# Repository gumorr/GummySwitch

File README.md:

# GummySwitch

1 MB ROM switch for Amigas with 1 MB ROM mods (can also work with 2 MB ROMs)

## Use

Position 1-2 on the jumper selects ROM 2 (U4), while position 2-3 selects ROM 1 (U3)

### BOM 
 
|Component|Location|QTY|
|---------|--------|---|
|1x21 Machined Pin Headers|U2|2|
|[42 Pin DIP Socket](https://www.mouser.com/ProductDetail/517-4842-6000-CP)|U3,U4|2|
|[74HCT00 SOIC](https://www.mouser.com/ProductDetail/595-SN74HCT00DE4)|U1|1|
|[0.1uF Ceramic capacitor, 0805](https://www.mouser.com/ProductDetail/581-08055C104K)|C1|1|
|[10K Resistor, 0805](https://www.mouser.com/ProductDetail/754-RR1220P-103D)|R1|1|

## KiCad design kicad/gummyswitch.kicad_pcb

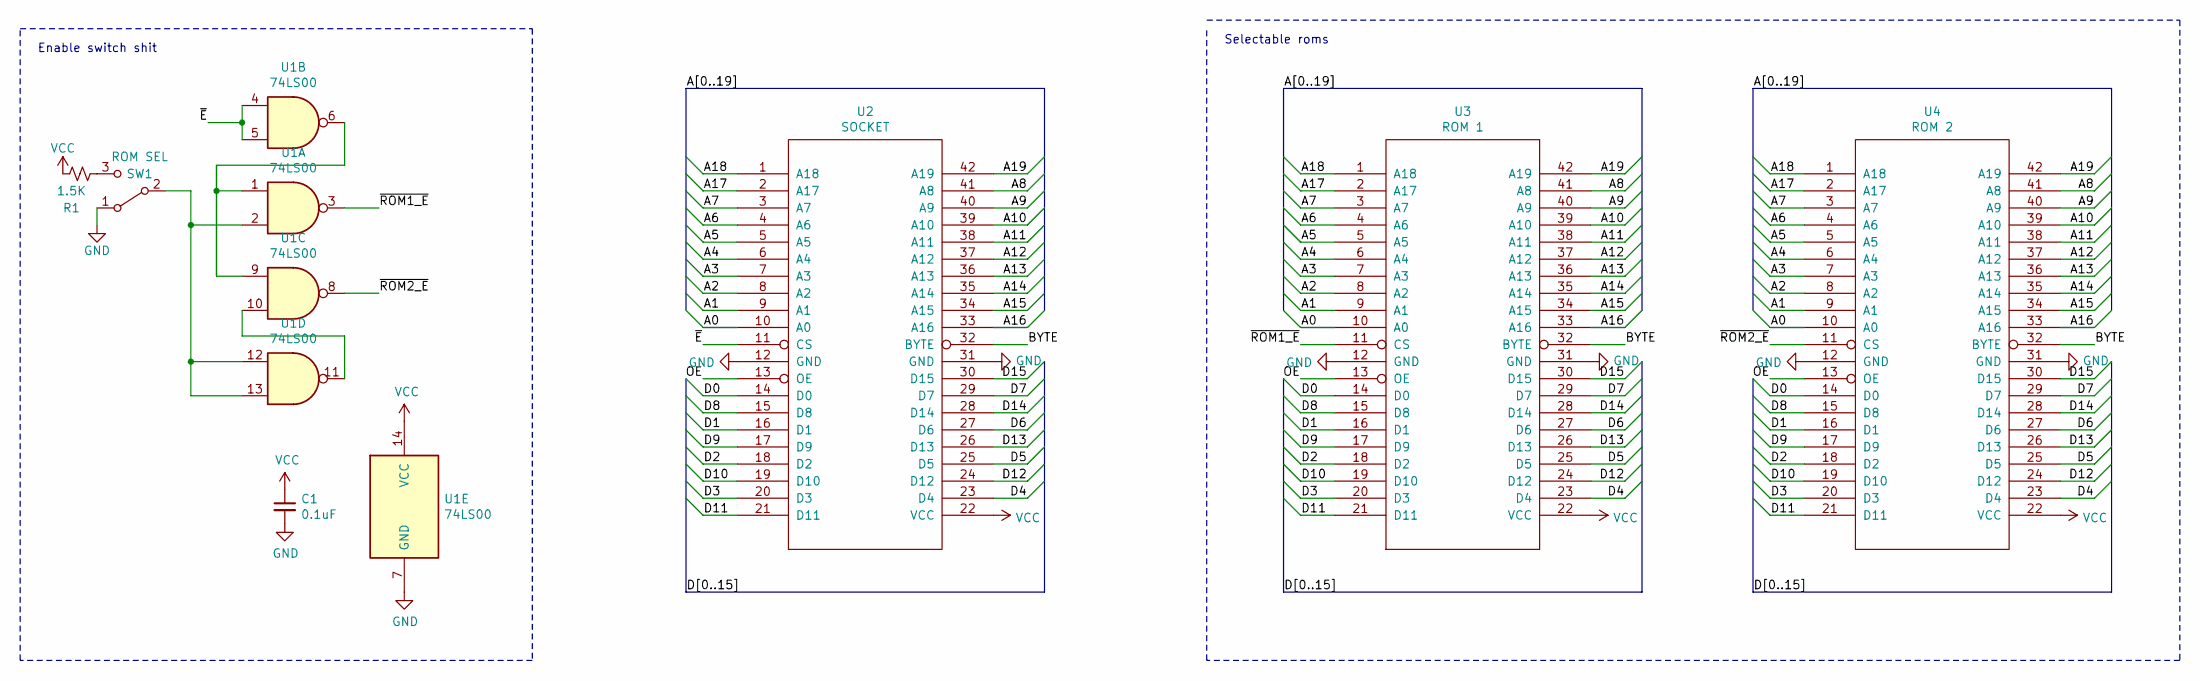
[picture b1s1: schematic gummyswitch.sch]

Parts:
C1: 0.1uF; C_0805_2012Metric_Pad1.18x1.45mm_HandSolder
R1: 1.5K; R_0805_2012Metric_Pad1.20x1.40mm_HandSolder
SW1: ROM SEL; PinHeader_1x04_P2.54mm_Horizontal
U1: 74LS00; SOIC-14_3.9x8.7mm_P1.27mm
U2: SOCKET; DIP-42_W15.24mm
U3: ROM 1; DIP-42_W15.24mm
U4: ROM 2; DIP-42_W15.24mm

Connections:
/A0: U2.10 (A0), U3.10 (A0), U4.10 (A0)
/A1: U2.9 (A1), U3.9 (A1), U4.9 (A1)
/A2: U2.8 (A2), U3.8 (A2), U4.8 (A2)
/A3: U2.7 (A3), U3.7 (A3), U4.7 (A3)
/A4: U2.6 (A4), U3.6 (A4), U4.6 (A4)
/A5: U2.5 (A5), U3.5 (A5), U4.5 (A5)
/A6: U2.4 (A6), U3.4 (A6), U4.4 (A6)
/A7: U2.3 (A7), U3.3 (A7), U4.3 (A7)
/A8: U2.41 (A8), U3.41 (A8), U4.41 (A8)
/A9: U2.40 (A9), U3.40 (A9), U4.40 (A9)
/A10: U2.39 (A10), U3.39 (A10), U4.39 (A10)
/A11: U2.38 (A11), U3.38 (A11), U4.38 (A11)
/A12: U2.37 (A12), U3.37 (A12), U4.37 (A12)
/A13: U2.36 (A13), U3.36 (A13), U4.36 (A13)
/A14: U2.35 (A14), U3.35 (A14), U4.35 (A14)
/A15: U2.34 (A15), U3.34 (A15), U4.34 (A15)
/A16: U2.33 (A16), U3.33 (A16), U4.33 (A16)
/A17: U2.2 (A17), U3.2 (A17), U4.2 (A17)
/A18: U2.1 (A18), U3.1 (A18), U4.1 (A18)
/A19: U2.42 (A19), U3.42 (A19), U4.42 (A19)
/BYTE: U2.32 (BYTE), U3.32 (BYTE), U4.32 (BYTE)
/D0: U2.14 (D0), U3.14 (D0), U4.14 (D0)
/D1: U2.16 (D1), U3.16 (D1), U4.16 (D1)
/D2: U2.18 (D2), U3.18 (D2), U4.18 (D2)
/D3: U2.20 (D3), U3.20 (D3), U4.20 (D3)
/D4: U2.23 (D4), U3.23 (D4), U4.23 (D4)
/D5: U2.25 (D5), U3.25 (D5), U4.25 (D5)
/D6: U2.27 (D6), U3.27 (D6), U4.27 (D6)
/D7: U2.29 (D7), U3.29 (D7), U4.29 (D7)
/D8: U2.15 (D8), U3.15 (D8), U4.15 (D8)
/D9: U2.17 (D9), U3.17 (D9), U4.17 (D9)
/D10: U2.19 (D10), U3.19 (D10), U4.19 (D10)
/D11: U2.21 (D11), U3.21 (D11), U4.21 (D11)
/D12: U2.24 (D12), U3.24 (D12), U4.24 (D12)
/D13: U2.26 (D13), U3.26 (D13), U4.26 (D13)
/D14: U2.28 (D14), U3.28 (D14), U4.28 (D14)
/D15: U2.30 (D15), U3.30 (D15), U4.30 (D15)
/OE: U2.13 (OE), U3.13 (OE), U4.13 (OE)
/~E: U1.4, U1.5, U2.11 (CS)
/~ROM1_E: U1.3, U3.11 (CS)
/~ROM2_E: U1.8, U4.11 (CS)
GND: C1.2, SW1.1 (A), U1.7 (GND), U2.12 (GND), U2.31 (GND), U3.12 (GND), U3.31 (GND), U4.12 (GND), U4.31 (GND)
unnamed: R1.1, SW1.3 (C)
unnamed: SW1.2 (B), U1.2, U1.12, U1.13
unnamed: U1.1, U1.6, U1.9
unnamed: U1.10, U1.11
VCC: C1.1, R1.2, U1.14 (VCC), U2.22 (VCC), U3.22 (VCC), U4.22 (VCC)

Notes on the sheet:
Enable switch shit
Selectable roms

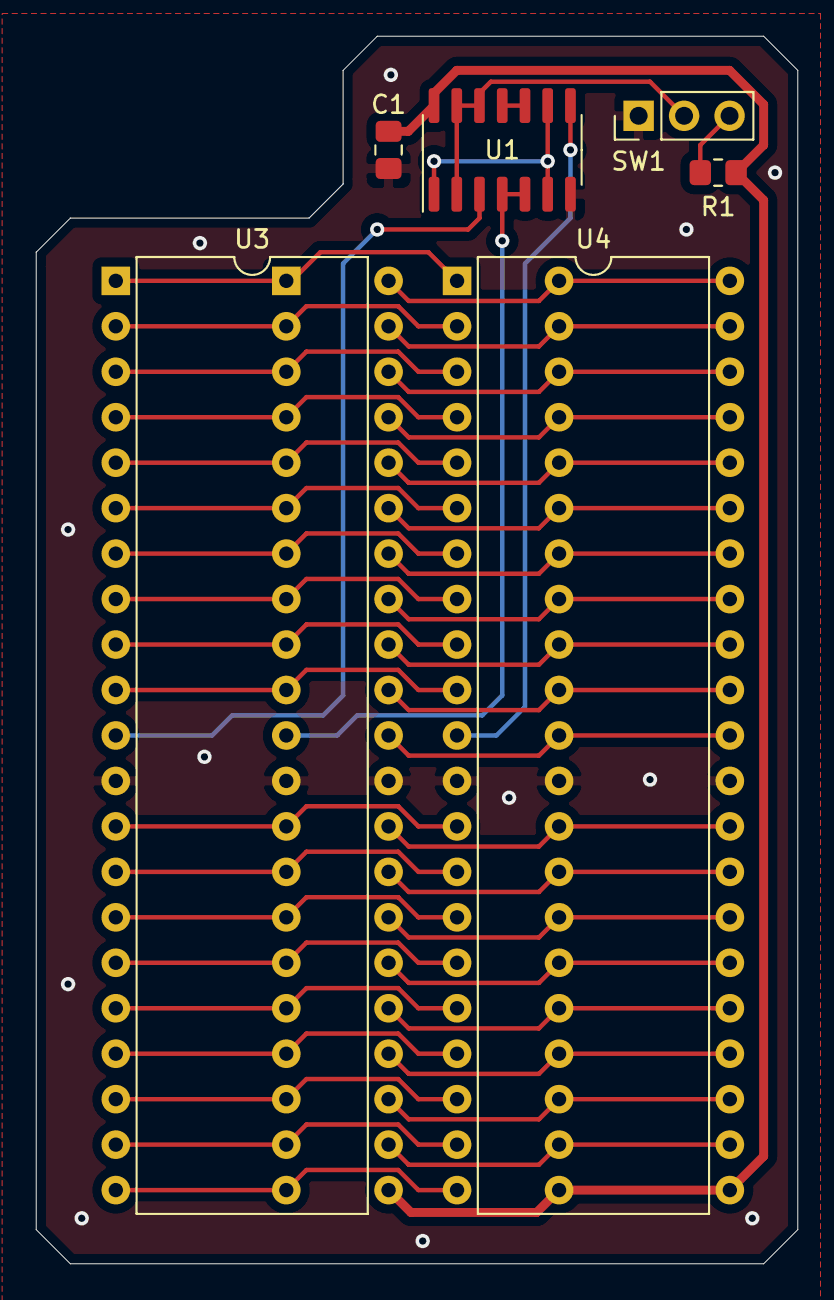
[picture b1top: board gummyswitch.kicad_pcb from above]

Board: 2 copper layers, 42.5 x 68.6 mm, 7 parts (0 on the bottom side), 47 nets.

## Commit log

2022-03-31 made the repository
